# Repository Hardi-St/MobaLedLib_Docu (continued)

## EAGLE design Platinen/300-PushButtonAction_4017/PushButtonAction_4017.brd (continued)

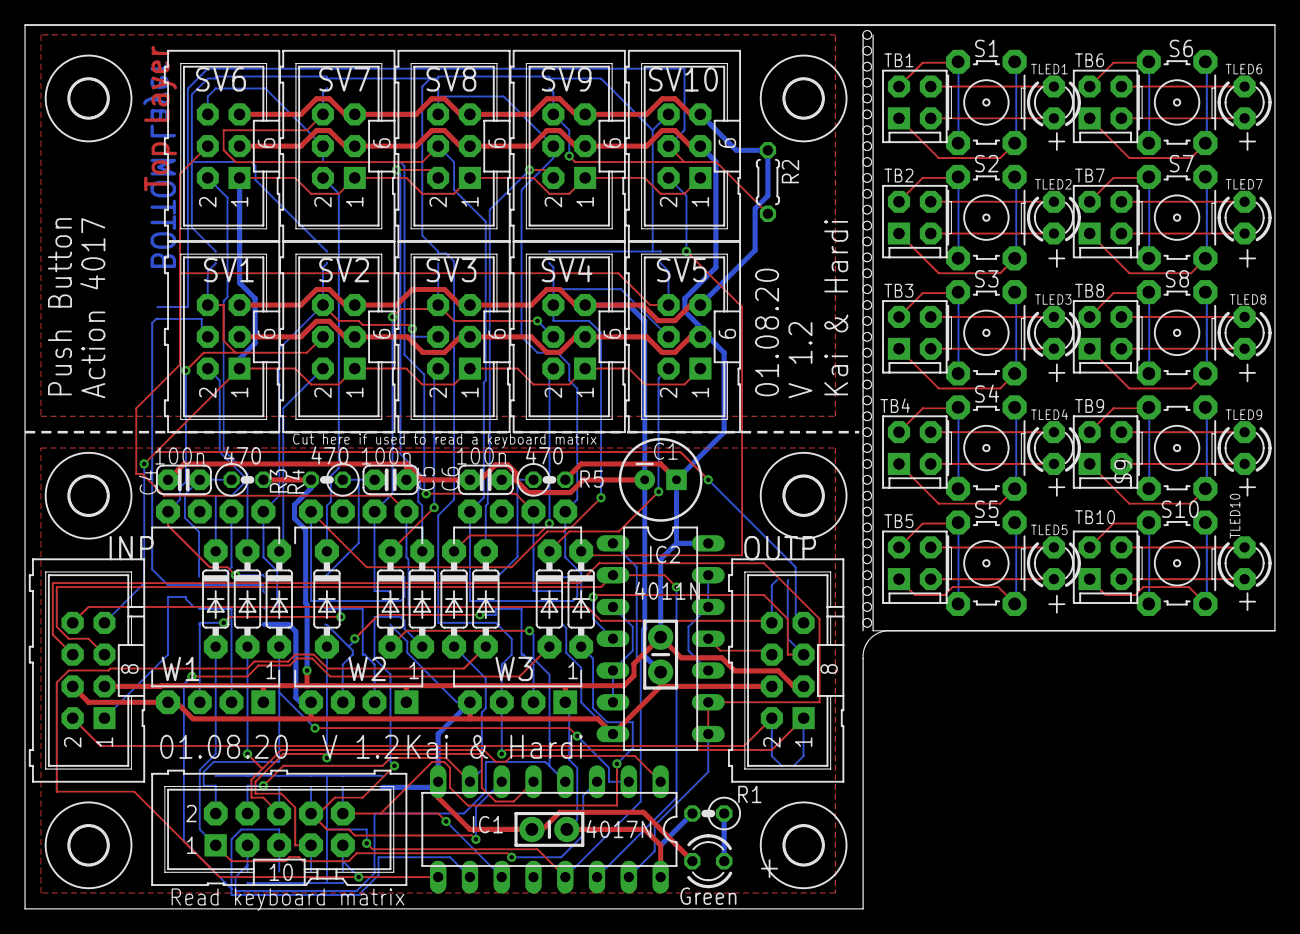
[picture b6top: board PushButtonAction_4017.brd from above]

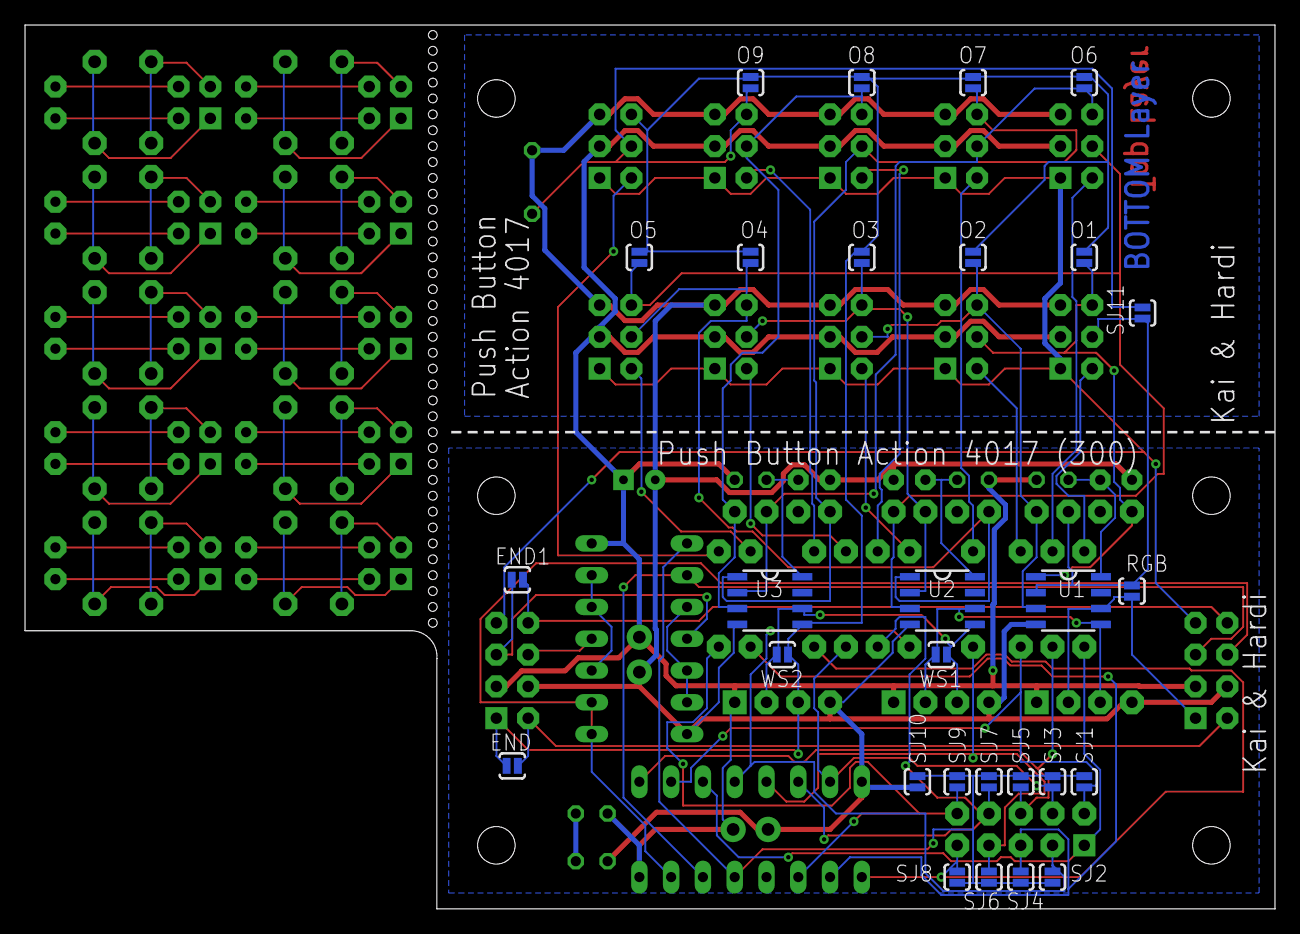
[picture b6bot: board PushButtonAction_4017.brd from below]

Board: 2 copper layers, 99.9 x 70.6 mm, 104 parts (28 on the bottom side), 90 nets.
